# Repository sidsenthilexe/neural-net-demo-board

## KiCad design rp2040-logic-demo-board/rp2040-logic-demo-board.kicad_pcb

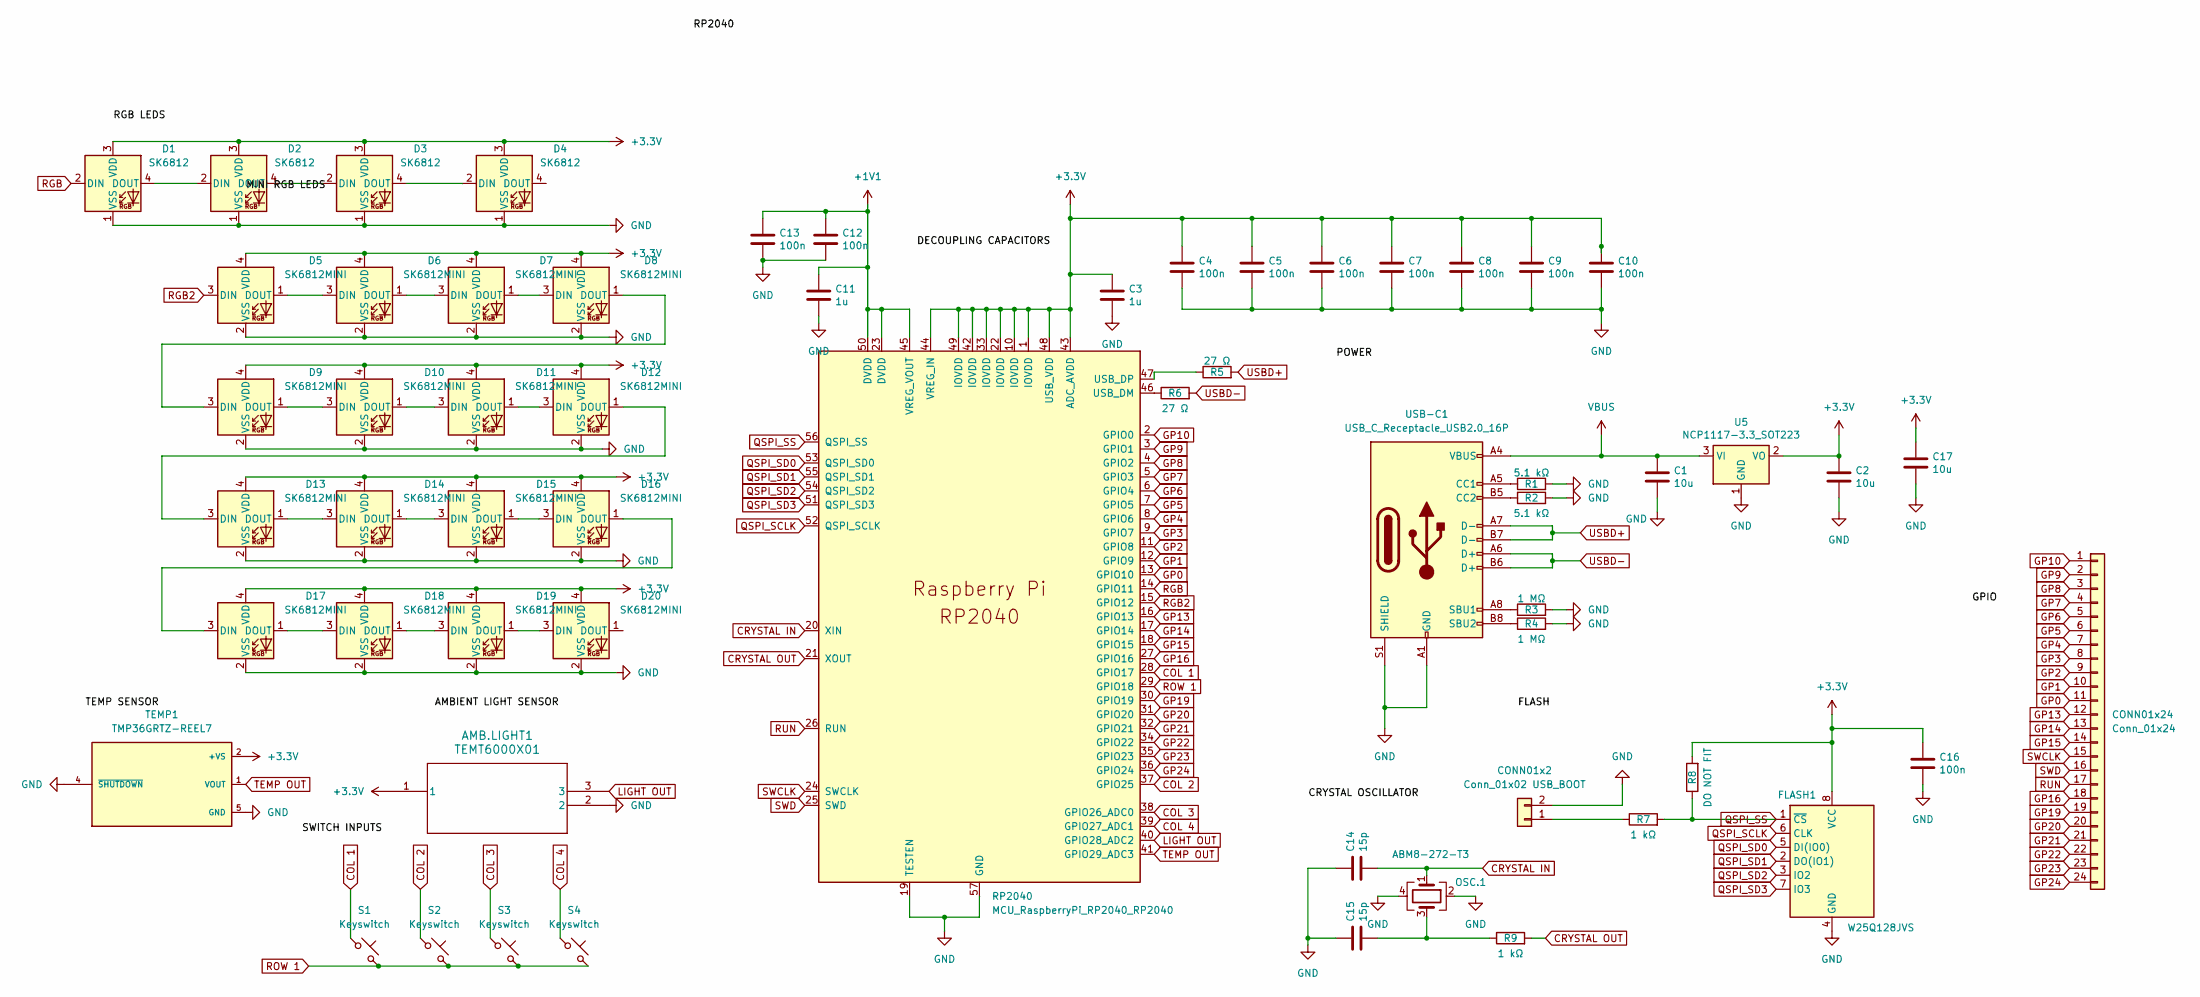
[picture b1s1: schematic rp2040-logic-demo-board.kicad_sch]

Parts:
AMB.LIGHT1: TEMT6000X01; SMT_6000X01_VIS
C1, C2, C17: 10u; C_0805_2012Metric
C3, C11: 1u; C_0402_1005Metric
C4, C5, C6, C7, C8, C9, C10, C12, C13, C16: 100n; C_0402_1005Metric
C14, C15: 15p; C_0402_1005Metric
CONN01x2: Conn_01x02 USB_BOOT; PinHeader_1x02_P1.00mm_Vertical
CONN01x24: Conn_01x24; PinHeader_1x24_P1.00mm_Vertical
D1, D2, D3, D4: SK6812; LED_SK6812_PLCC4_5.0x5.0mm_P3.2mm
D5, D6, D7, D8, D9, D10, D11, D12, D13, D14, D15, D16, D17, D18, D19, D20: SK6812MINI; LED_SK6812MINI_PLCC4_3.5x3.5mm_P1.75mm
FLASH1: W25Q128JVS; SOIC-8_5.23x5.23mm_P1.27mm
OSC.1: ABM8-272-T3; Crystal_SMD_3225-4Pin_3.2x2.5mm
R1, R2: 5.1 kΩ; R_0402_1005Metric
R3, R4: 1 MΩ; R_0402_1005Metric
R5, R6: 27 Ω; R_0402_1005Metric
R7, R9: 1 kΩ; R_0402_1005Metric
R8: DO NOT FIT; R_0402_1005Metric
RP2040: MCU_RaspberryPi_RP2040_RP2040; RP2040-QFN-56
S1, S2, S3, S4: Keyswitch; MX_PCB_1.00u
TEMP1: TMP36GRTZ-REEL7; SOT95P280X145-5N; PARTREV H
U5: NCP1117-3.3_SOT223; SOT-223-3_TabPin2
USB-C1: USB_C_Receptacle_USB2.0_16P; USB_C_Receptacle_GCT_USB4105-xx-A_16P_TopMnt_Horizontal

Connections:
+1V1: C11.1, C12.1, C13.1, RP2040.23 (DVDD), RP2040.45 (VREG_VOUT), RP2040.50 (DVDD)
+3.3V: AMB.LIGHT1.1, C2.1, C3.1, C4.1, C5.1, C6.1, C7.1, C8.1, C9.1, C10.1, C16.1, C17.1, D1.3 (VDD), D2.3 (VDD), D3.3 (VDD), D4.3 (VDD), D5.4 (VDD), D6.4 (VDD), D7.4 (VDD), D8.4 (VDD), D9.4 (VDD), D10.4 (VDD), D11.4 (VDD), D12.4 (VDD), D13.4 (VDD), D14.4 (VDD), D15.4 (VDD), D16.4 (VDD), D17.4 (VDD), D18.4 (VDD), D19.4 (VDD), D20.4 (VDD), FLASH1.8 (VCC), R8.2, RP2040.1 (IOVDD), RP2040.10 (IOVDD), RP2040.22 (IOVDD), RP2040.33 (IOVDD), RP2040.42 (IOVDD), RP2040.43 (ADC_AVDD), RP2040.44 (VREG_IN), RP2040.48 (USB_VDD), RP2040.49 (IOVDD), TEMP1.2 (+VS), U5.2 (VO)
COL 1: RP2040.28 (GPIO17), S1.1
COL 2: RP2040.37 (GPIO25), S2.1
COL 3: RP2040.38 (GPIO26_ADC0), S3.1
COL 4: RP2040.39 (GPIO27_ADC1), S4.1
CRYSTAL IN: C14.2, OSC.1.1, RP2040.20 (XIN)
CRYSTAL OUT: R9.2, RP2040.21 (XOUT)
GND: AMB.LIGHT1.2, C1.2, C2.2, C3.2, C4.2, C5.2, C6.2, C7.2, C8.2, C9.2, C10.2, C11.2, C12.2, C13.2, C14.1, C15.1, C16.2, C17.2, CONN01x2.2, D1.1 (VSS), D2.1 (VSS), D3.1 (VSS), D4.1 (VSS), D5.2 (VSS), D6.2 (VSS), D7.2 (VSS), D8.2 (VSS), D9.2 (VSS), D10.2 (VSS), D11.2 (VSS), D12.2 (VSS), D13.2 (VSS), D14.2 (VSS), D15.2 (VSS), D16.2 (VSS), D17.2 (VSS), D18.2 (VSS), D19.2 (VSS), D20.2 (VSS), FLASH1.4 (GND), OSC.1.2, OSC.1.4, R1.2, R2.2, R3.2, R4.2, RP2040.19 (TESTEN), RP2040.57 (GND), TEMP1.4 (~SHUTDOWN), TEMP1.5 (GND), U5.1 (GND), USB-C1.A1 (GND), USB-C1.A12 (GND), USB-C1.B1 (GND), USB-C1.B12 (GND), USB-C1.S1 (SHIELD)
GP0: CONN01x24.11, RP2040.13 (GPIO10)
GP1: CONN01x24.10, RP2040.12 (GPIO9)
GP2: CONN01x24.9, RP2040.11 (GPIO8)
GP3: CONN01x24.8, RP2040.9 (GPIO7)
GP4: CONN01x24.7, RP2040.8 (GPIO6)
GP5: CONN01x24.6, RP2040.7 (GPIO5)
GP6: CONN01x24.5, RP2040.6 (GPIO4)
GP7: CONN01x24.4, RP2040.5 (GPIO3)
GP8: CONN01x24.3, RP2040.4 (GPIO2)
GP9: CONN01x24.2, RP2040.3 (GPIO1)
GP10: CONN01x24.1, RP2040.2 (GPIO0)
GP13: CONN01x24.12, RP2040.16 (GPIO13)
GP14: CONN01x24.13, RP2040.17 (GPIO14)
GP15: CONN01x24.14, RP2040.18 (GPIO15)
GP16: CONN01x24.18, RP2040.27 (GPIO16)
GP19: CONN01x24.19, RP2040.30 (GPIO19)
GP20: CONN01x24.20, RP2040.31 (GPIO20)
GP21: CONN01x24.21, RP2040.32 (GPIO21)
GP22: CONN01x24.22, RP2040.34 (GPIO22)
GP23: CONN01x24.23, RP2040.35 (GPIO23)
GP24: CONN01x24.24, RP2040.36 (GPIO24)
LIGHT OUT: AMB.LIGHT1.3, RP2040.40 (GPIO28_ADC2)
unnamed: C15.2, OSC.1.3, R9.1
unnamed: CONN01x2.1, R7.1
unnamed: D1.4 (DOUT), D2.2 (DIN)
unnamed: D2.4 (DOUT), D3.2 (DIN)
unnamed: D3.4 (DOUT), D4.2 (DIN)
unnamed: D5.1 (DOUT), D6.3 (DIN)
unnamed: D6.1 (DOUT), D7.3 (DIN)
unnamed: D7.1 (DOUT), D8.3 (DIN)
unnamed: D8.1 (DOUT), D9.3 (DIN)
unnamed: D9.1 (DOUT), D10.3 (DIN)
unnamed: D10.1 (DOUT), D11.3 (DIN)
unnamed: D11.1 (DOUT), D12.3 (DIN)
unnamed: D12.1 (DOUT), D13.3 (DIN)
unnamed: D13.1 (DOUT), D14.3 (DIN)
unnamed: D14.1 (DOUT), D15.3 (DIN)
unnamed: D15.1 (DOUT), D16.3 (DIN)
unnamed: D16.1 (DOUT), D17.3 (DIN)
unnamed: D17.1 (DOUT), D18.3 (DIN)
unnamed: D18.1 (DOUT), D19.3 (DIN)
unnamed: D19.1 (DOUT), D20.3 (DIN)
unnamed: R6.1, RP2040.46 (USB_DM)
unnamed: R5.1, RP2040.47 (USB_DP)
unnamed: R1.1, USB-C1.A5 (CC1)
unnamed: R2.1, USB-C1.B5 (CC2)
unnamed: R3.1, USB-C1.A8 (SBU1)
unnamed: R4.1, USB-C1.B8 (SBU2)
QSPI_SCLK: FLASH1.6 (CLK), RP2040.52 (QSPI_SCLK)
QSPI_SD0: FLASH1.5 (DI(IO0)), RP2040.53 (QSPI_SD0)
QSPI_SD1: FLASH1.2 (DO(IO1)), RP2040.55 (QSPI_SD1)
QSPI_SD2: FLASH1.3 (IO2), RP2040.54 (QSPI_SD2)
QSPI_SD3: FLASH1.7 (IO3), RP2040.51 (QSPI_SD3)
QSPI_SS: FLASH1.1 (~CS), R7.2, R8.1, RP2040.56 (QSPI_SS)
RGB: D1.2 (DIN), RP2040.14 (GPIO11)
RGB2: D5.3 (DIN), RP2040.15 (GPIO12)
ROW 1: RP2040.29 (GPIO18), S1.2, S2.2, S3.2, S4.2
RUN: CONN01x24.17, RP2040.26 (RUN)
SWCLK: CONN01x24.15, RP2040.24 (SWCLK)
SWD: CONN01x24.16, RP2040.25 (SWD)
TEMP OUT: RP2040.41 (GPIO29_ADC3), TEMP1.1 (VOUT)
USBD+: R5.2, USB-C1.A7 (D-), USB-C1.B7 (D-)
USBD-: R6.2, USB-C1.A6 (D+), USB-C1.B6 (D+)
VBUS: C1.1, U5.3 (VI), USB-C1.A4 (VBUS), USB-C1.A9 (VBUS), USB-C1.B4 (VBUS), USB-C1.B9 (VBUS)

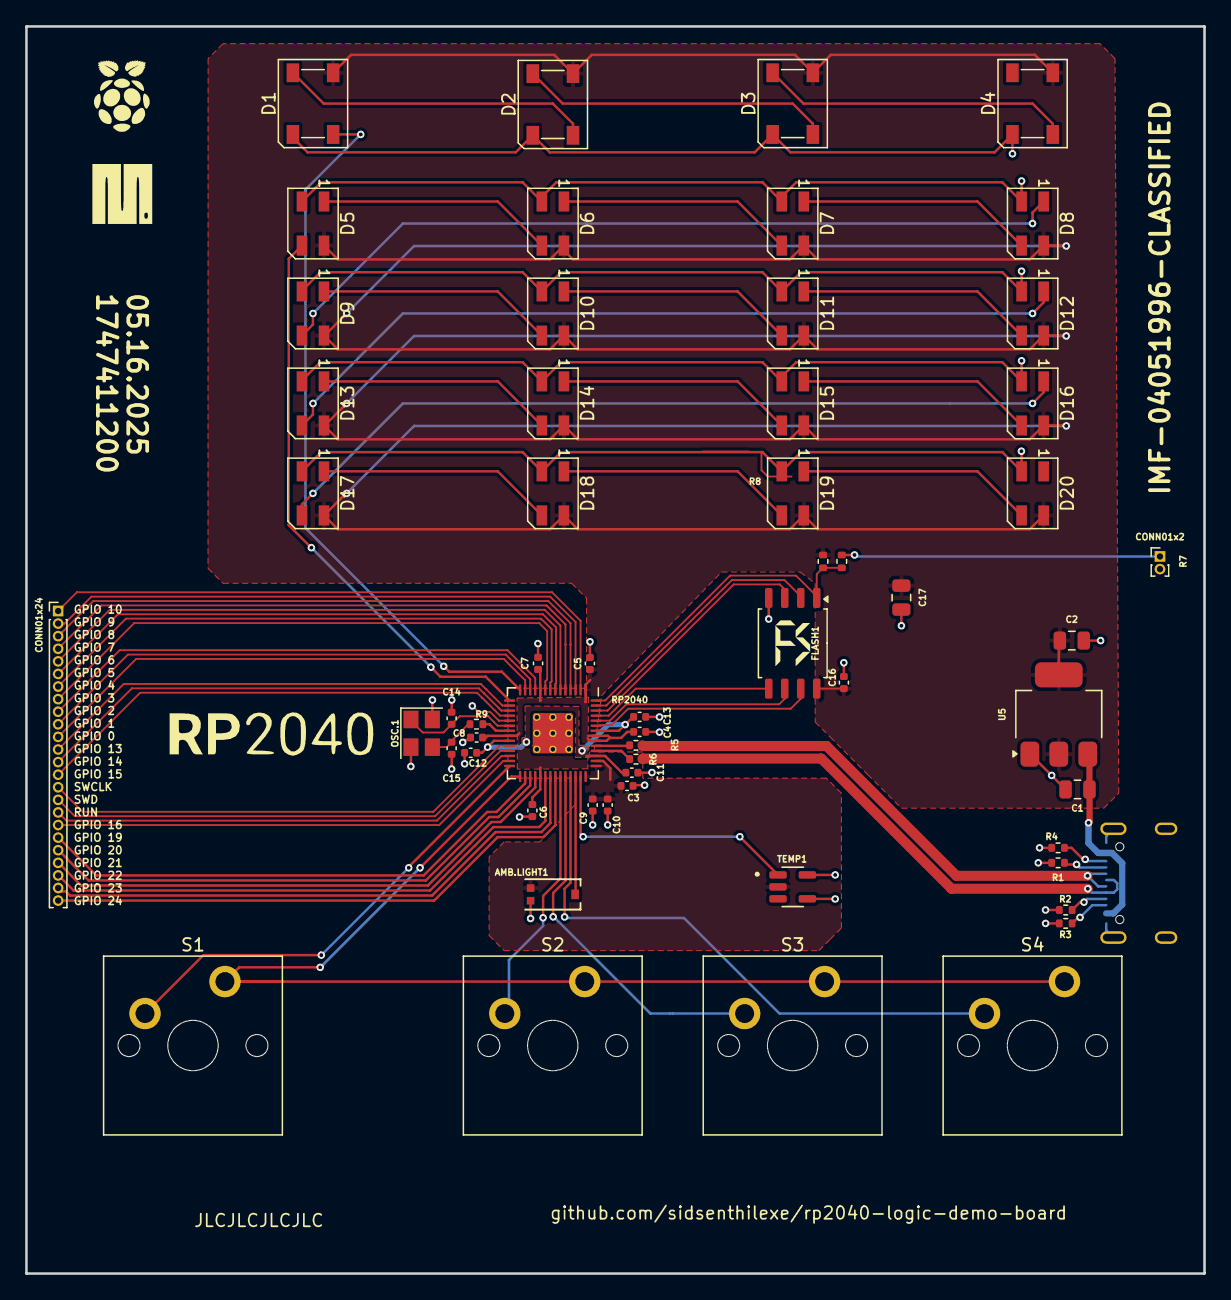
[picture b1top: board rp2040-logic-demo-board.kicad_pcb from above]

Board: 2 copper layers, 93.6 x 99.0 mm, 59 parts (1 on the bottom side), 73 nets.

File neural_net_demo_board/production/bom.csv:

Designator,Footprint,Quantity,Value,LCSC Part #
AMB.LIGHT1,SMT_6000X01_VIS,1,TEMT6000X01,
"C1, C17, C2",0805,3,10u,
"C10, C12, C13, C16, C4, C5, C6, C7, C8, C9",0402,10,100n,
"C11, C3",0402,2,1u,
"C14, C15",0402,2,15p,
CONN01X2,PinHeader_1x02_P1.00mm_Vertical,1,Conn_01x02 USB_BOOT,
"D1, D2, D3, D4",LED_SK6812_PLCC4_5.0x5.0mm_P3.2mm,4,SK6812,
"D10, D11, D12, D13, D14, D15, D16, D17, D18, D19, D20, D5, D6, D7, D8, D9",LED_SK6812MINI_PLCC4_3.5x3.5mm_P1.75mm,16,SK6812MINI,
FLASH1,SOIC-8_5.23x5.23mm_P1.27mm,1,W25Q128JVS,
OSC.1,Crystal_SMD_3225-4Pin_3.2x2.5mm,1,ABM8-272-T3,
"R1, R2",0402,2,5.1 kΩ,
"R3, R4",0402,2,1 MΩ,
"R5, R6",0402,2,27 Ω,
"R7, R9",0402,2,1 kΩ,
R8,0402,1,DO NOT FIT,
RP2040,RP2040-QFN-56,1,MCU_RaspberryPi_RP2040_RP2040,
"S1, S2, S3, S4",MX_PCB_1.00u,4,Keyswitch,
TEMP1,SOT95P280X145-5N,1,TMP36GRTZ-REEL7,
U5,SOT-223-3_TabPin2,1,NCP1117-3.3_SOT223,
USB-C1,USB_C_Receptacle_GCT_USB4105-xx-A_16P_TopMnt_Horizontal,1,USB_C_Receptacle_USB2.0_16P,

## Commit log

2025-04-29 Added input io, started working on minimum hardware design for rp2040
2025-05-02 Integrate rp2040, input/outputs
2025-05-05 pcb's basically done atp
2025-05-06 starting to learn tensorflow
2025-05-07 chore: delete tf.py
2025-05-08 updated name
    because i had no idea what i was going to do for software when i started this
2025-05-08 create 2 files and update 1 file
2025-05-08 update boot.py logic for lighting up main and confidence leds
